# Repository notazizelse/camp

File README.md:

# CAMP v2 — TechnoCamp Circuitry Class Board

**A CubeSat payload computer you can build in a weekend.**

An 80 × 80 mm Arduino Nano carrier board that turns a handful of loose sensor modules
into one tidy instrument: it reads the temperature, the humidity and the carbon-monoxide
level of the air around it, shows them on a small screen, and reports them over USB —
the same job the payload computer of a real CubeSat does.

Every part is through-hole, so it can be assembled with a soldering iron and no
magnifying glass. The board carries no chips of its own — the Arduino Nano does all the
thinking. What the board gives you is clean wiring, the right resistors in the right
places, and connectors that only fit one way.

> 🇺🇿 **Bu hujjatning o'zbekcha versiyasi: [README.uz.md](README.uz.md)**
> 🔧 Designing a rev C, or want the netlist and fab notes? → [docs/hardware-reference.md](docs/hardware-reference.md)

---

## Table of contents

- [What you need](#what-you-need)
- [How the board works](#how-the-board-works)
- [The schematic](#the-schematic)
- [Build it](#build-it)
- [Flash it](#flash-it)
- [Use it](#use-it)
- [Things to try](#things-to-try)
- [When it does not work](#when-it-does-not-work)
- [Repository layout](#repository-layout)
- [Opening the project in KiCad](#opening-the-project-in-kicad)
- [Getting the board made](#getting-the-board-made)
- [Credits](#credits)

---

## What you need

### Parts that go on the board

| Ref | Qty | Part | Notes |
|---|---|---|---|
| ARDUINO1 | 1 | Arduino Nano (ATmega328P) | Use two 1×15 female headers so the Nano can be unplugged |
| R4 – R9 | 6 | 220 Ω resistor, ¼ W | Colour bands: red–red–brown–gold |
| LED1, LED2 | 2 | 4-pin RGB LED, 5 mm | Fitted in 1×4 **sockets**, so they can be swapped |
| SW1, SW2, SW3 | 3 | 6 × 6 mm tactile push button | 4-leg, 5 mm tall |
| J5 "SEL" | 1 | 1×3 pin header + jumper cap | Chooses common-cathode or common-anode LEDs |
| DHT11 | 1 | 1×3 pin header | For the temperature / humidity module |
| MQ-7 | 1 | 1×4 pin header | For the carbon-monoxide module |
| LCD | 1 | 1×4 pin header | For the I²C display module |
| U1 | 1 | 2-way 5 mm screw terminal | **Mounted on the back of the board** |
| H1 – H4 | 4 | M3 screw + standoff | Optional, for mounting into a frame |

The full machine-readable list, with LCSC order codes, is in
[`campv2/production/bom.csv`](campv2/production/bom.csv).

### Modules that plug into the board

- **DHT11** temperature + humidity module (3-pin version)
- **MQ-7** carbon-monoxide module (4-pin version, with both analogue and digital outputs)
- **16 × 2 LCD with an I²C backpack** (a small board soldered to the back of the display
  with only 4 pins: GND, VCC, SDA, SCL)
- **2 × common-cathode RGB LEDs**, 4 legs each

### Tools

Soldering iron, solder, side cutters, a small screwdriver for the terminal, and a
computer with the Arduino IDE.

---

## How the board works

Read it left to right. The three things on the left **tell** the Arduino something. The
two things on the right are how the Arduino **tells you** something. Nothing on this
board talks to anything else directly — every signal goes through the Nano.

### The pin map

This is the single most important table in the repository. It is what the board *is*.

| Arduino pin | Goes to | What it does |
|---|---|---|
| `D2` | DHT11 pin 2 | Temperature and humidity data (one wire, both values) |
| `A7` | MQ-7 pin 1 | CO level, as a voltage — **analogue in only, cannot be a digital pin** |
| `D12` | MQ-7 pin 2 | The MQ-7 module's own alarm output |
| `A0` | SW1 | "Next screen" button |
| `A1` | SW2 | "Previous screen" button |
| `D8` | SW3 | "Change units" button (°C ↔ °F) |
| `A4` | LCD pin 3 | I²C **SDA** — data |
| `A5` | LCD pin 4 | I²C **SCL** — clock |
| `D3` `D5` `D6` | LED1 via R4, R5, R6 | Red, green, blue of the first RGB LED |
| `D9` `D10` `D11` | LED2 via R7, R8, R9 | Red, green, blue of the second RGB LED |
| `VIN` | U1 pin 1 | 5 V from the screw terminal |
| `GND` | U1 pin 2, every module, H1–H4 | Ground |

All six LED pins are PWM-capable, which is why the LEDs can fade smoothly between
colours instead of only switching on and off.

### Three details worth understanding

**The buttons have no resistors.** Each button connects its Arduino pin to GND, and
nothing else. The pull-up resistor that holds the pin HIGH lives *inside* the ATmega328P
and is switched on in software with `pinMode(pin, INPUT_PULLUP)`. So a button reads
`HIGH` when it is not pressed and `LOW` when it is — backwards from what you might
expect, and a classic thing to get stuck on.

**J5 decides which way the LEDs are wired.** A 4-pin RGB LED has three separate colour
legs and one leg they all share. On a *common-cathode* LED that shared leg must go to
GND; on a *common-anode* LED it must go to +5 V. Rather than pick one and lock you in,
this board brings the shared leg out to the middle pin of J5, marked `SEL` on the
silkscreen, with `−` (GND) on one side and `+` (5 V) on the other. Put the jumper cap on
the side your LEDs need, and set `COMMON_ANODE` in the sketch to match.

**Each LED colour gets its own 220 Ω resistor.** An LED will happily draw enough current
to destroy itself, and the three colours inside an RGB package have different forward
voltages, so one shared resistor would make the colours uneven. Six resistors, one per
colour channel: R4/R5/R6 for LED1, R7/R8/R9 for LED2.

---

## The schematic

Higher-resolution vector version: [`docs/images/schematic.svg`](docs/images/schematic.svg).
The KiCad source is [`campv2/campv2.kicad_sch`](campv2/campv2.kicad_sch).

The drawing is deliberately split into labelled boxes — *Buttons*, *Temp & Humid*,
*Gas*, *Screen*, *Mounting holes*, and the two LED blocks — so you can read one idea at a
time. Instead of drawing a wire all the way from the Nano to each block, the schematic
uses **net labels**: two wire ends carrying the same label, like `A4`, are the same
electrical node even though no line connects them on paper. This is how real schematics
stay readable.

---

## Build it

Full step-by-step version with photos of each stage: [`docs/assembly.md`](docs/assembly.md).
The short version:

Solder from **shortest part to tallest**, so that each time you flip the board over, the
parts you have already fitted hold themselves flat against it.

1. **R4 – R9**, the six 220 Ω resistors. They lie flat. Direction does not matter.
2. **SW1, SW2, SW3**, the tactile buttons. They only drop in one way round.
3. **J5**, the 3-pin `SEL` header.
4. **DHT11 / MQ-7 / LCD** headers (3, 4 and 4 pins).
5. **LED1, LED2** sockets — 1×4 female headers, not the LEDs themselves.
6. **ARDUINO1** — two 1×15 female headers. Fit the Nano into them *before* soldering so
   they end up parallel, then solder one pin at each end, check it is square, and finish.
7. **U1**, the screw terminal — **on the back of the board**, wire openings facing out.

Then plug in the modules, put a jumper cap on J5, and drop the Nano into its socket with
the USB connector facing the edge of the board (the silkscreen shows you where).

> ⚠️ **Power the board from USB *or* the screw terminal — never both at once.**
> The screw terminal feeds the Nano's `VIN` pin. Feeding 5 V into `VIN` while USB is also
> connected puts the Nano's regulator and your USB port in a fight neither wins.

---

## Flash it

The sketch is [`campv2/firmware/CubeSat/CubeSat.ino`](campv2/firmware/CubeSat/CubeSat.ino).

1. Install the Arduino IDE.
2. Install three libraries via **Tools → Manage Libraries…**
   - `LiquidCrystal I2C` by Frank de Brabander
   - `DHT sensor library` by Adafruit
   - `Adafruit Unified Sensor` by Adafruit
   *(No internet in the classroom? Known-good copies are vendored in
   [`Arduino/libraries/`](Arduino/libraries/) — see the README there.)*
3. **Tools → Board → Arduino Nano**, **Tools → Processor → ATmega328P**.
   If uploading fails with a `avrdude: stk500_recv()` error, switch the processor to
   **ATmega328P (Old Bootloader)**. Most cheap Nano clones need this.
4. Open `CubeSat.ino`, put your own name in `STUDENT_NAME`, and press Upload.

### Settings you are meant to change

They are all together at the top of the sketch, in the block marked
`PART 1 — SETTINGS YOU ARE MEANT TO CHANGE`:

| Setting | What it is for |
|---|---|
| `STUDENT_NAME` | Shown on the LCD at start-up |
| `LCD_ADDRESS` | `0x27` for most I²C backpacks; try `0x3F` if the screen stays blank |
| `COMMON_ANODE` | `false` for common-cathode LEDs (J5 on `−`), `true` for common-anode (J5 on `+`) |
| `TEMP_COLD_C`, `TEMP_HOT_C` | When LED1 turns blue and when it turns red |
| `CO_WARNING_PPM`, `CO_DANGER_PPM` | When LED2 turns amber and when it turns red |
| `CALIBRATE_MODE`, `MQ7_R0` | MQ-7 calibration — see below |

Everything below that block is the wiring, and changing it will simply stop the board
from matching the copper.

---

## Use it

The LCD shows one screen at a time. **SW1** walks forward through them, **SW2** walks
back, and they wrap around:

```
   NAME  →  TEMPERATURE  →  HUMIDITY  →  CARBON MONOXIDE
     ↑                                          │
     └──────────────────────────────────────────┘
```

**SW3** switches the temperature between °C and °F.

The two RGB LEDs are status lights, exactly like the ones on a real satellite:

| | LED1 — temperature | LED2 — air quality |
|---|---|---|
| 🔵 blue | below 18 °C | — |
| 🟢 green | comfortable | CO below 35 ppm |
| 🟡 amber | — | CO 35 – 200 ppm |
| 🔴 red | above 28 °C | CO above 200 ppm |

Open the **Serial Monitor at 9600 baud** and the board reports every reading once a
second. That is your ground station.

### Calibrating the MQ-7

An MQ-7 does not measure CO directly — it measures its own resistance, which changes when
CO touches it. To turn that into a number in ppm the sketch needs `R0`, the sensor's
resistance in *clean* air, and every sensor's `R0` is different.

1. Set `CALIBRATE_MODE = true` and upload.
2. Leave the board in fresh air, powered, for a few minutes.
3. Read the number printed in the Serial Monitor, copy it into `MQ7_R0`.
4. Set `CALIBRATE_MODE = false` and upload again.

Until you do this, treat the ppm figure as "roughly" rather than "actually". Also give the
sensor about 20 seconds after power-on before believing anything — its heater has to come
up to temperature first, and the screen says `warming up` while it does.

---

## Things to try

The board was designed to be poked at. Some starting points, roughly in order of
difficulty:

1. Change the temperature thresholds so the LED turns red when you breathe on the sensor.
2. Add a fifth screen showing how long the board has been running.
3. Make LED2 pulse instead of sitting at a steady colour when CO is in the warning band.
4. Log the serial output to a file and plot a day of temperature readings.
5. Use the MQ-7's digital alarm pin (`D12`) to flash both LEDs at once.
6. Replace the DHT11 with a DHT22 — same 3 pins, better accuracy. What changes in the code?
7. Sketch a rev C: what would you add if you had two more pins?

---

## When it does not work

The full list is in [`docs/troubleshooting.md`](docs/troubleshooting.md). The four that
catch nearly everybody:

| Symptom | Almost always |
|---|---|
| LCD backlight is on but shows nothing, or white squares | Wrong I²C address — change `LCD_ADDRESS` from `0x27` to `0x3F` |
| Upload fails, `stk500_recv(): programmer is not responding` | Wrong bootloader — **Tools → Processor → ATmega328P (Old Bootloader)** |
| LEDs are on when they should be off, colours inverted | J5 jumper and `COMMON_ANODE` disagree — flip one of them |
| Temperature reads `nan` or the screen says the sensor failed | DHT11 in backwards, or its middle pin not seated |

---

## Repository layout

```
camp/
├── README.md                    ← you are here (English)
├── README.uz.md                 ← same thing, in Uzbek
├── CHANGELOG.md                 ← what changed between board revisions
│
├── campv2/                      ← THE BOARD, and everything that belongs to it
│   ├── campv2.kicad_pro         ·  open this one in KiCad
│   ├── campv2.kicad_sch         ·  schematic
│   ├── campv2.kicad_pcb         ·  layout
│   ├── fp-lib-table             ·  points at ../lib (project-relative)
│   ├── sym-lib-table
│   │
│   ├── firmware/
│   │   └── CubeSat/CubeSat.ino  ← THE CODE. Open this in the Arduino IDE
│   │
│   └── production/              ← WHAT THE FACTORY GETS. Do not edit by hand
│       ├── …PCB_B.zip           ·  upload this file to JLCPCB / PCBWay as-is
│       ├── bom.csv              ·  parts list with LCSC codes
│       ├── positions.csv        ·  pick-and-place positions
│       ├── designators.csv
│       └── netlist.ipc          ·  for the fab's electrical test
│
├── lib/                         ← shared KiCad libraries
│   ├── lcsc/                    ·  symbols + footprints pulled from LCSC
│   └── 3d/                      ·  STEP models for the 3D viewer
│
├── production/                  ← artwork and reference plots. NOT the fab
│   ├── turin_logo2.kicad_mod    ·  package — that is in campv2/production/
│   ├── assotsiatsiya_logo…      ·  the two logos printed on the back
│   ├── logo*.kicad_mod          ·  earlier versions of them
│   ├── campv2-*.pdf             ·  copper and outline plots, for checking
│   └── 3d.step                  ·  the assembled board, for mechanical fit
│
├── Arduino/libraries/           ← offline copies of the three Arduino libraries
│
├── docs/
│   ├── hardware-reference.md    ← for engineers: nets, design rules, how to modify
│   ├── assembly.md              ← for students: build it step by step
│   ├── troubleshooting.md
│   └── images/                  ← every picture used in these documents
│
├── lcsc.py, lcsc.txt            ← pulls a KiCad part from an LCSC order code
│
└── archive/                     ← OLD WORK. Nothing here is used by the current board
    ├── camp/                    ·  rev A, superseded
    ├── camp_demo/               ·  a tiny one-LED teaching board
    └── camp_t9/                 ·  an empty project stub
```

**The rule:** everything the current board needs is inside `campv2/` — schematic,
layout, sketch and fab package, one folder. `lib/` is what KiCad loads behind the
scenes. `docs/` is for you. Nobody needs `archive/`.

> ⚠️ **Two folders are called `production`, and they are not the same thing.**
> `campv2/production/` is the fab package — the gerbers, BOM and pick-and-place
> file you send to the factory. The top-level `production/` holds the logo
> footprints and reference plots. "Send them the production files" means the zip
> in `campv2/production/`.

---

## Opening the project in KiCad

You need **KiCad 10.0 or newer** — the files use the 2026 file format and older KiCad
will refuse to open them.

```bash
git clone https://github.com/notazizelse/camp.git
cd camp
```

Then open `campv2/campv2.kicad_pro`. That is all. There is no "configure paths"
step, no environment variables to set, and no libraries to install:

- The symbol and footprint libraries are found through `${KIPRJMOD}`, KiCad's built-in
  "wherever this project happens to be" variable, so they resolve on any machine.
- The 3D models resolve the same way.
- Everything the board actually uses lives inside this repository.

If KiCad still complains about a missing library, that is a bug in this repository —
please open an issue rather than fixing it locally, so the next person does not hit it.

---

## Getting the board made

Upload `campv2/production/TechnoCamp_Circuitry_Class_PCB_B.zip` to any PCB house
without unzipping it, and take the defaults:

| Setting | Value |
|---|---|
| Size | 80 × 80 mm |
| Layers | 2 |
| Thickness | 1.6 mm |
| Min track / clearance | 0.5 mm / 0.5 mm |
| Min hole | 0.3 mm |
| Vias | none — every connection is a track or a pad |
| Surface finish | HASL is fine |

The design rules are deliberately loose — nothing on this board is near any fab's limits,
which is what makes it cheap and reliable to produce in class quantities.

The board has a **+5 V pour on the front and a GND pour on the back**. That gives every
part a low-impedance path to both rails without routing a single power track, and it is
why the back of the board looks almost empty.

Across the top of the back, above the mounting holes, the board carries
**PER ASPERA AD ASTRA** — *through hardships, to the stars.*

---

## Credits

Designed by **Azizbek N** for **TechnoCamp 2026**, run by the Robotics and Engineering
Association at **Turin Polytechnic University in Tashkent**. Both logos are printed on the
back of the board.

The Arduino Nano pinout reference embedded in the schematic is from
[Last Minute Engineers](https://lastminuteengineers.com/) and is used for reference only.

**Licence:** not yet chosen. Until one is added, treat this as "ask before reusing".
For a teaching board like this, the usual pairing is
[CERN-OHL-P v2](https://ohwr.org/cern_ohl_p_v2.txt) for the hardware and MIT for the
firmware.

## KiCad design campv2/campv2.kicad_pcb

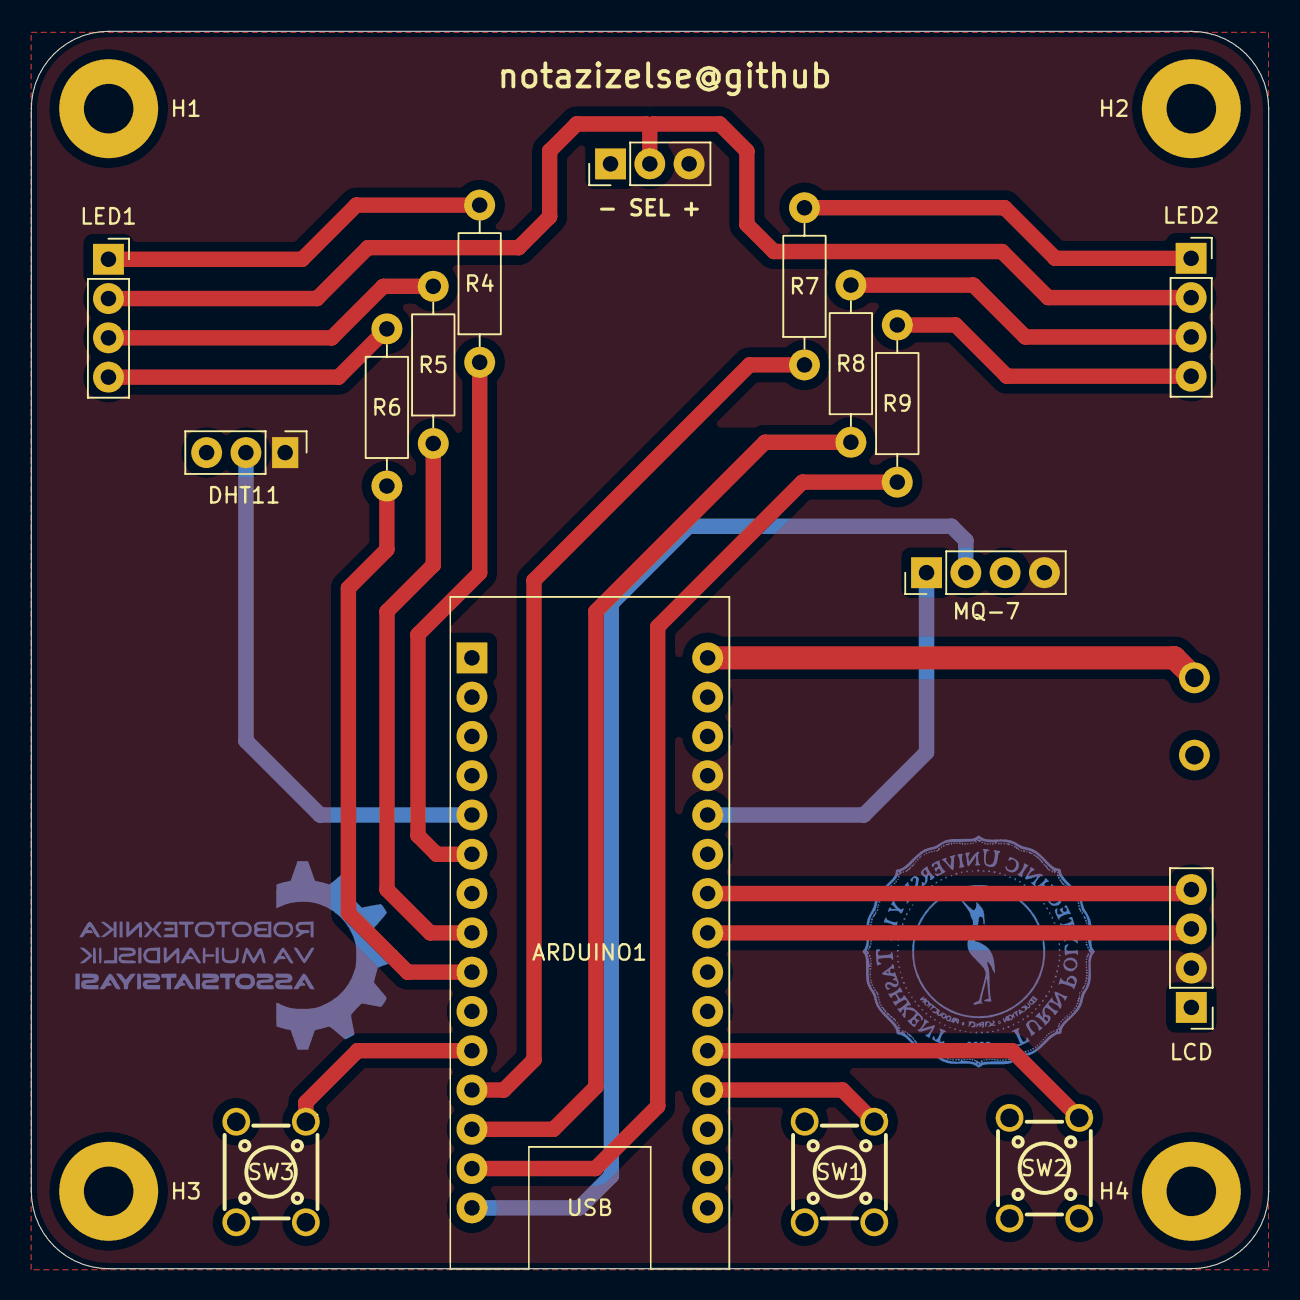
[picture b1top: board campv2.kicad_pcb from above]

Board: 2 copper layers, 80.0 x 80.0 mm, 21 parts (1 on the bottom side), 24 nets.

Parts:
ARDUINO1: Arduino_Nano
DHT11: DHT11; PinHeader_1x03_P2.54mm_Vertical
H1, H2, H3, H4: MountingHole_Pad; MountingHole_3.2mm_M3_Pad
J5: LED_SEL; PinHeader_1x03_P2.54mm_Vertical
LCD: LCD; PinHeader_1x04_P2.54mm_Vertical
LED1, LED2: TJ-L5FCMXHTCSLCRGB-A5; PinSocket_1x04_P2.54mm_Vertical
MQ-7: MQ-7; PinHeader_1x04_P2.54mm_Vertical
R4, R5, R6, R7, R8, R9: 220; R_Axial_DIN0207_L6.3mm_D2.5mm_P10.16mm_Horizontal
SW1, SW2, SW3: button; SW-TH_4P-L6.0-W6.0-P4.50-LS6.5
U1: screw terminal; CONN-TH_DEGSON_DG301-5.0-02P

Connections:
+5V: ARDUINO1.27 (+5V), DHT11.1, J5.3, LCD.2, MQ-7.4
/A0: ARDUINO1.19 (A0), SW1.1
/A1: ARDUINO1.20 (A1), SW2.1
/A4: ARDUINO1.23 (A4), LCD.3
/A5: ARDUINO1.24 (A5), LCD.4
/A7: ARDUINO1.26 (A7), MQ-7.1
/D2: ARDUINO1.5 (D2), DHT11.2
/D3: ARDUINO1.6 (D3), R4.1
/D5: ARDUINO1.8 (D5), R5.1
/D6: ARDUINO1.9 (D6), R6.1
/D8: ARDUINO1.11 (D8), SW3.1
/D9: ARDUINO1.12 (D9), R7.1
/D10: ARDUINO1.13 (D10), R8.1
/D11: ARDUINO1.14 (D11), R9.1
/D12: ARDUINO1.15 (D12), MQ-7.2
GND: ARDUINO1.4 (GND), ARDUINO1.29 (GND), DHT11.3, H1.1 (1_1), H2.1 (1_1), H3.1 (1_1), H4.1 (1_1), J5.1, LCD.1, MQ-7.3, SW1.4, SW2.4, SW3.4, U1.2
unnamed: J5.2, LED1.2 (A), LED2.2 (A)
unnamed: LED1.1 (A), R4.2
unnamed: LED1.3 (A), R5.2
unnamed: LED1.4 (A), R6.2
unnamed: LED2.1 (A), R7.2
unnamed: LED2.3 (A), R8.2
unnamed: LED2.4 (A), R9.2
VCC: ARDUINO1.30 (VIN), U1.1
